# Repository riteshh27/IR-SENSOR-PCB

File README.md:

# IR Sensor PCB

A KiCad hardware project for a simple IR (infrared) sensor module, featuring an onboard comparator circuit, sensitivity adjustment, and status indication.

## Overview

This board implements a classic IR obstacle/proximity sensor design: an IR emitter/receiver pair feeds into a comparator IC, with a potentiometer to tune detection sensitivity and an LED to indicate detection state. Designed in KiCad.

## Bill of Materials

 Designator | Description        | Footprint                                    | Qty |

 D1, D2     | LED                | LED_D3.0mm_Horizontal_O1.27mm_Z2.0mm_Clear   | 2   |
 D3         | LED (status)       | LED_1206_3216Metric                          | 1   |
 J1         | 3-pin header       | PinHeader_1x03_P2.54mm_Horizontal            | 1   |
 R1, R2     | Resistor, 10k      | R_1206_3216Metric                            | 2   |
 R3         | Resistor, 10k      | R_1210_3225Metric                            | 1   |
 RV1        | Potentiometer, 10k | Bourns 3296W (vertical trimmer)              | 1   |
 U1         | 8-pin IC (comparator, e.g. LM358/LM393) | DIP-8 (0.3", 7.62mm)    | 1   |

> Note: U1's exact part isn't labeled in the netlist — most 3-pin IR sensor modules of this type use a dual op-amp/comparator (LM358 or LM393) in a DIP-8 package. Confirm against your schematic before ordering.

## Board Details

- **Layers:** 2-layer (F.Cu / B.Cu)
- **Board thickness:** 0.063 in (~1.6 mm, standard)
- **Front copper area:** 0.429 in²
- **Back copper area:** 0.077 in²
- **Min track width / clearance:** 0.0079 in (~0.2 mm)
- **Min drill diameter:** 0.0118 in (~0.3 mm)
- **Components:** 9 total (5 THT, 4 SMD), all on the front side
- **Pads:** 18 through-hole, 8 SMD
- **Vias:** 4 through-vias

## Connector (J1)

A 3-pin header, typically wired as:

| Pin | Function |
|-----|----------|
| 1   | VCC      |
| 2   | GND      |
| 3   | OUT (digital detection signal) |

> Confirm actual pinout against the schematic (`IR_SENSOR.kicad_sch`) before wiring.

## Repository Contents

 File                      Description                                  
 `IR_SENSOR.kicad_pro`    | KiCad project file                           
 `IR_SENSOR.kicad_sch`    | Schematic                                     
 `IR_SENSOR.kicad_pcb`    | PCB layout                                    
 `IR_SENSOR.kicad_prl`    | Local project settings (layer visibility etc.)
 `IR_SENSOR.csv`          | Bill of materials (BOM)                       
 `IR_SENSOR.rpt`          | KiCad DRC/electrical rules report             
 `IR_SENSOR_report.txt`   | PCB statistics report (board area, pads, vias)

## Getting Started

1. Install [KiCad](https://www.kicad.org/) (version 7 or later recommended).
2. Clone this repository:
   ```bash
   git clone https://github.com/riteshh27/IR-SENSOR-PCB.git
   ```
3. Open `IR_SENSOR.kicad_pro` in KiCad to view/edit the schematic and PCB layout.

## Manufacturing

To generate Gerber files for fabrication:
1. Open the PCB layout in KiCad.
2. Go to **File → Fabrication Outputs → Gerbers**.
3. Export the drill file alongside the Gerbers.
4. Zip the output folder and upload to your preferred PCB fab (JLCPCB, PCBWay, etc.).

## License

See [LICENSE](LICENSE) for details.

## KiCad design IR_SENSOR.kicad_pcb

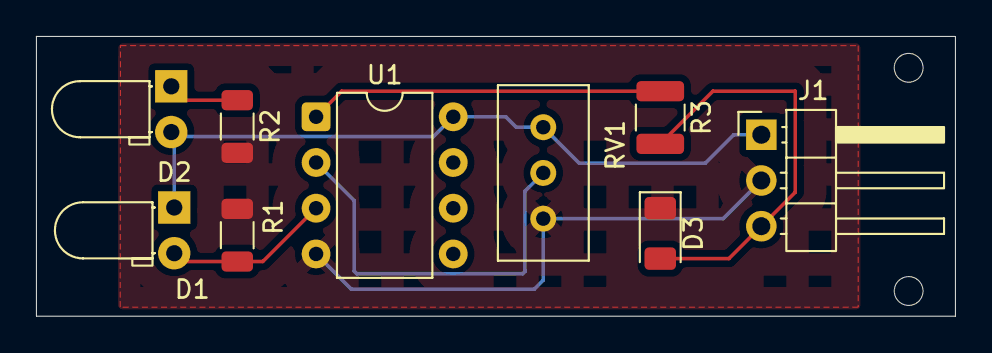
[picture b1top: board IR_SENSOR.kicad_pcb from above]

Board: 2 copper layers, 51.1 x 15.5 mm, 9 parts (0 on the bottom side), 7 nets.

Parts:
D1, D2: LED; LED_D3.0mm_Horizontal_O1.27mm_Z2.0mm_Clear
D3: LED; LED_1206_3216Metric
J1: PinHeader_1x03_P2.54mm_Horizontal
R1, R2: 10k; R_1206_3216Metric
R3: 10k; R_1210_3225Metric
RV1: 10k; Potentiometer_Bourns_3296W_Vertical
U1: DIP-8_W7.62mm

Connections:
/out: D3.2 (A), J1.3, R3.2
GND: D3.1 (K), J1.2, R1.2, R2.2, RV1.3, U1.4 (V-)
unnamed: D1.2 (A), R1.1, U1.3 (+)
unnamed: D2.1 (K), R2.1
unnamed: R3.1, U1.1
unnamed: RV1.2, U1.2 (-)
VCC: D1.1 (K), D2.2 (A), J1.1, RV1.1, U1.8 (V+)
